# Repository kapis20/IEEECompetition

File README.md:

# IEEECompetition
This is the repo for IEEE Pitch Competition codes and files storage 

To run the code, you will need

1) Open CV (for windows: py -m pip install opencv-python)
2) numpy (for windows: py -m pip install numpy)
3) MediaPipe (for windows: pip install mediapipe) 

Note: Both squat and lateral raise code are essentially the same except for the angle calculation and display.

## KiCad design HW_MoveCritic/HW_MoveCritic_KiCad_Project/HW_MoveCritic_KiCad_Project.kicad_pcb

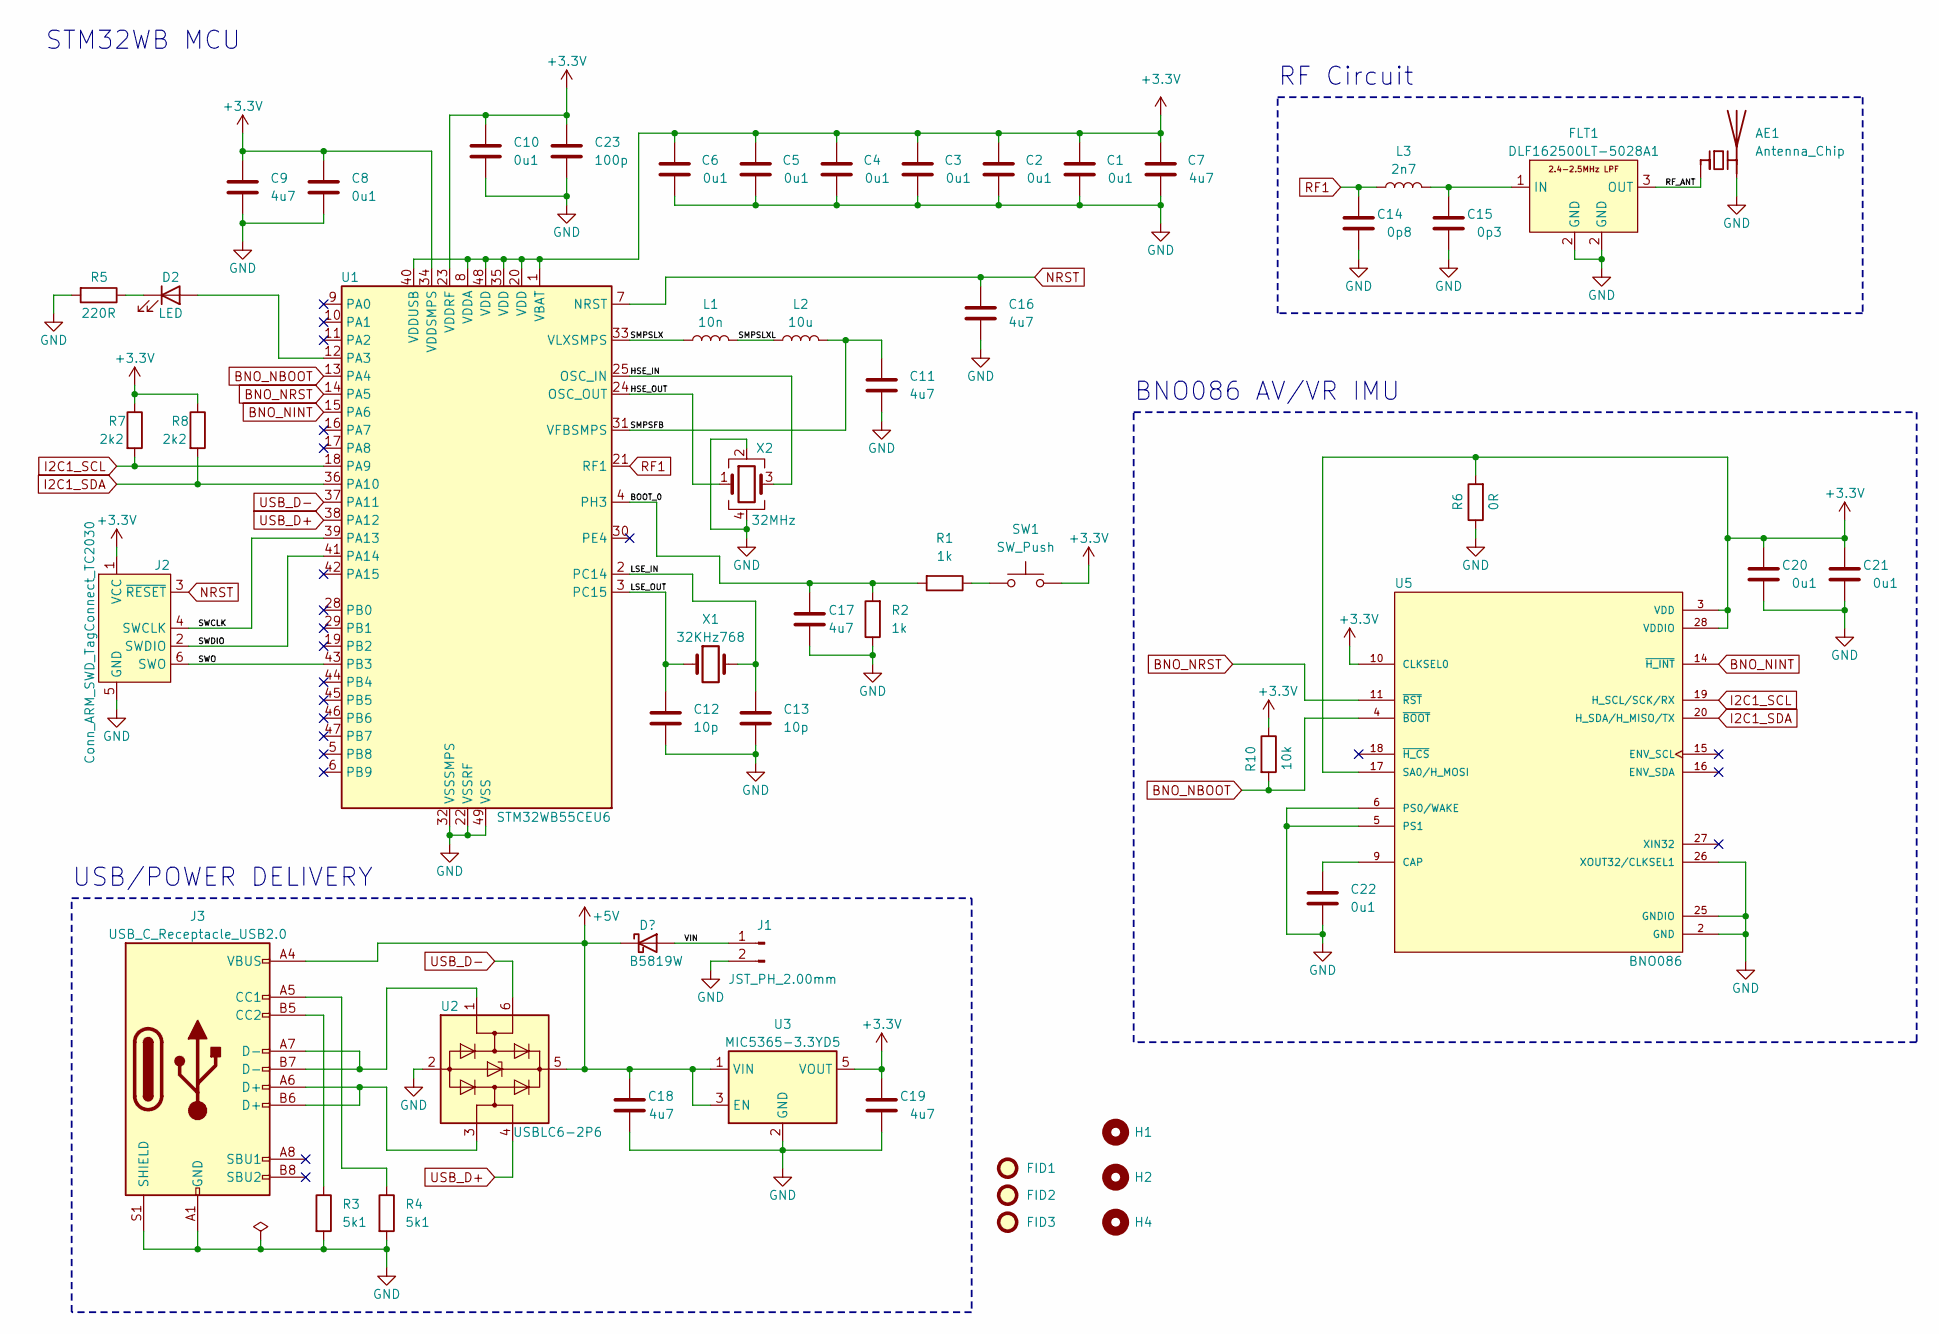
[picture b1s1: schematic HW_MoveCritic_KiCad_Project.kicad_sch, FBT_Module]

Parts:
AE1: Antenna_Chip; 2400MHz_PCB_Inverted_F
C1, C2, C3, C4, C5, C6, C8, C10, C20, C21, C22: 0u1; C_0201_0603Metric
C7, C9, C11, C16, C17, C18, C19: 4u7; C_0201_0603Metric
C12, C13: 10p; C_0402_1005Metric
C14: 0p8; C_0402_1005Metric
C15: 0p3; C_0402_1005Metric
C23: 100p; C_0201_0603Metric
D1: B5819W; D_SOD-123
D2: LED; LED_0402_1005Metric
FID1, FID2, FID3: Fiducial; Fiducial_1mm_Mask2mm
FLT1: DLF162500LT-5028A1
H1, H2, H4: MountingHole; MountingHole_2.2mm_M2_DIN965
J1: JST_PH_2.00mm; JST_PH_B2B-PH-K_1x02_P2.00mm_Vertical
J2: Conn_ARM_SWD_TagConnect_TC2030; Tag-Connect_TC2030-IDC-FP_2x03_P1.27mm_Vertical
J3: USB_C_Receptacle_USB2.0; USB_C_Receptacle_GCT_USB4105-xx-A_16P_TopMnt_Horizontal
L1: 10n; L_0402_1005Metric
L2: 10u; L_0805_2012Metric
L3: 2n7; L_0402_1005Metric
R1, R2: 1k; R_0603_1608Metric
R3, R4: 5k1; R_0402_1005Metric
R5: 220R; R_0201_0603Metric
R6: 0R; R_0603_1608Metric
R7, R8: 2k2; R_0402_1005Metric
R10: 10k; R_0402_1005Metric
SW1: SW_Push; PinHeader_1x02_P2.54mm_Vertical
U1: STM32WB55CEU6; QFN-48-1EP_7x7mm_P0.5mm_EP5.6x5.6mm
U2: USBLC6-2P6; SOT-666
U3: MIC5365-3.3YD5; SOT-23-5
U5: BNO086; LGA-28_5.2x3.8mm_P0.5mm; PARTREV 1.6
X1: 32KHz768; 830009678
X2: 32MHz; Crystal_SMD_TXC_7M-4Pin_3.2x2.5mm

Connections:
+3.3V: C1.1, C2.1, C3.1, C4.1, C5.1, C6.1, C7.1, C8.1, C9.1, C10.1, C19.1, C20.1, C21.1, C23.1, J2.1 (VCC), R6.2, R7.1, R8.1, R10.1, SW1.2, U1.1 (VBAT), U1.8 (VDDA), U1.20 (VDD), U1.23 (VDDRF), U1.34 (VDDSMPS), U1.35 (VDD), U1.40 (VDDUSB), U1.48 (VDD), U3.5 (VOUT), U5.3 (VDD), U5.10 (CLKSEL0), U5.17 (SA0/H_MOSI), U5.28 (VDDIO)
+5V: C18.1, D1.1 (K), J3.A4 (VBUS), J3.A9 (VBUS), J3.B4 (VBUS), J3.B9 (VBUS), U2.5 (VBUS), U3.1 (VIN), U3.3 (EN)
/BOOT_0: C17.1, R1.2, R2.2, U1.4 (PH3)
/HSE_IN: U1.25 (OSC_IN), X2.3
/HSE_OUT: U1.24 (OSC_OUT), X2.1
/LSE_IN: C13.1, U1.2 (PC14), X1.2
/LSE_OUT: C12.1, U1.3 (PC15), X1.1
/RF_ANT: AE1.1 (FEED), FLT1.3 (OUT)
/SMPSFB: C11.1, L2.2, U1.31 (VFBSMPS)
/SMPSLX: L1.1, U1.33 (VLXSMPS)
/SMPSLXL: L1.2, L2.1
/SWCLK: J2.4 (SWCLK), U1.39 (PA13)
/SWDIO: J2.2 (SWDIO), U1.41 (PA14)
/SWO: J2.6 (SWO), U1.43 (PB3)
/VIN: D1.2 (A), J1.1
BNO_NBOOT: R10.2, U1.13 (PA4), U5.4 (~BOOT)
BNO_NINT: U1.15 (PA6), U5.14 (~H_INT)
BNO_NRST: U1.14 (PA5), U5.11 (~RST)
GND: AE1.2 (PCB_Trace), C1.2, C2.2, C3.2, C4.2, C5.2, C6.2, C7.2, C8.2, C9.2, C10.2, C11.2, C12.2, C13.2, C14.2, C15.2, C16.2, C17.2, C18.2, C19.2, C20.2, C21.2, C22.2, C23.2, FLT1.2 (GND), J1.2, J2.5 (GND), J3.A1 (GND), J3.A12 (GND), J3.B1 (GND), J3.B12 (GND), J3.S1 (SHIELD), R2.1, R3.2, R4.2, R5.2, R6.1, U1.22 (VSSRF), U1.32 (VSSSMPS), U1.49 (VSS), U2.2 (GND), U3.2 (GND), U5.2 (GND), U5.5 (PS1), U5.6 (PS0/WAKE), U5.25 (GNDIO), U5.26 (XOUT32/CLKSEL1), X2.2, X2.4
I2C1_SCL: R7.2, U1.18 (PA9), U5.19 (H_SCL/SCK/RX)
I2C1_SDA: R8.2, U1.36 (PA10), U5.20 (H_SDA/H_MISO/TX)
NRST: C16.1, J2.3 (~RESET), U1.7 (NRST)
unnamed: D2.2 (A), U1.12 (PA3)
unnamed: D2.1 (K), R5.1
unnamed: C15.1, FLT1.1 (IN), L3.2
unnamed: J3.A5 (CC1), R4.1
unnamed: J3.B5 (CC2), R3.1
unnamed: J3.A6 (D+), J3.B6 (D+), U2.3 (I/O2)
unnamed: J3.A7 (D-), J3.B7 (D-), U2.1 (I/O1)
unnamed: R1.1, SW1.1
unnamed: C22.1, U5.9 (CAP)
RF1: C14.1, L3.1, U1.21 (RF1)
USB_D+: U1.38 (PA12), U2.4 (I/O2)
USB_D-: U1.37 (PA11), U2.6 (I/O1)

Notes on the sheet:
USB/POWER DELIVERY
STM32WB MCU
BNO086 AV/VR IMU
RF Circuit

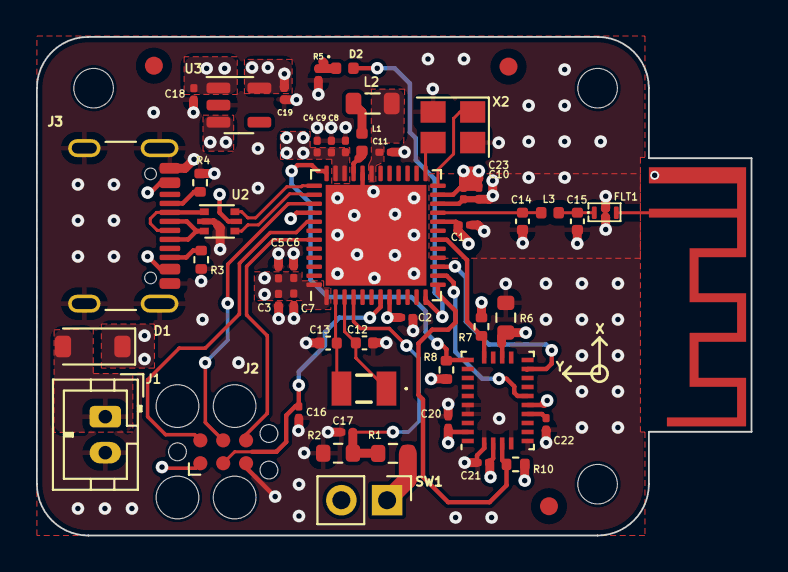
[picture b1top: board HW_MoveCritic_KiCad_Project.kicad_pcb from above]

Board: 4 copper layers, 39.7 x 27.7 mm, 55 parts (0 on the bottom side), 34 nets.

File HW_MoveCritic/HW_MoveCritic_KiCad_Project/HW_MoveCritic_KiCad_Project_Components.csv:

Source:,C:\Dev\IEEECompetition\HW_MoveCritic\HW_MoveCritic_KiCad_Project\HW_MoveCritic_KiCad_Project.kicad_sch,,,,,,,,
Date:,28/02/2024 13:18,,,,,,,,
Tool:,Eeschema 7.0.8,,,,,,,,
Generator:,C:\Program Files\KiCad\7.0\bin\scripting\plugins/bom_csv_grouped_by_value.py,,,,,,,,
Component Count:,45,,,,,,,,
,,,,,,,,,
Collated Components:,,,,,,,,,
,,,,,,,,,
Item,Qty,Reference(s),Value,LibPart,Footprint,Datasheet,Mfr_Part_Number,Price/unit (bulk 1000 units),Price/unit (prototype)
1,11,"C1, C2, C3, C4, C5, C6, C8, C10, C20, C21, C22",0u1,Device:C,Capacitor_SMD:C_0201_0603Metric,https://www.mouser.co.uk/datasheet/2/40/cx5r_KGM-3223198.pdf,KGM03AR51A104KN,0.063,0.344
2,7,"C7, C9, C11, C16, C17, C18, C19",4u7,Device:C,Capacitor_SMD:C_0201_0603Metric,https://www.mouser.co.uk/datasheet/2/40/cx5r_KGM-3223198.pdf,KGM03DR50J475MH,0.056,0.304
3,2,"C12, C13",10p,Device:C,Capacitor_SMD:C_0402_1005Metric,https://www.mouser.co.uk/datasheet/2/40/C0GNP0_KGM-3216332.pdf,KGM05ACG1C100KH,0.032,0.208
4,1,C14,0p8,Device:C,Capacitor_SMD:C_0402_1005Metric,https://www.mouser.co.uk/datasheet/2/447/KEM_C1121_CBR_AUTO-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,CBR04C808B5GACAUTO,0.015,0.128
5,1,C15,0p3,Device:C,Capacitor_SMD:C_0402_1005Metric,https://www.mouser.co.uk/datasheet/2/281/1/GRM1555C1HR30BA01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,GRM1555C1HR30BA01J,0.009,0.08
6,1,C23,100p,Device:C,Capacitor_SMD:C_0201_0603Metric,https://www.mouser.co.uk/datasheet/2/40/KGM_X7R-3223212.pdf,KGM03AR71H101KH,0.03,0.08
7,1,D1,B5819W,Device:D_Schottky,Diode_SMD:D_SOD-123,https://www.mouser.co.uk/datasheet/2/258/B5817W_B5819W_SOD_1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,B5819W-TP,0.031,0.216
8,1,D2,Red,Device:D_LED,Diode_SMD:C_0402_1005Metric,https://www.we-online.com/components/products/datasheet/1500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,150040RS73240,0.132,0.256
9,1,FLT1,DLF162500LT-5028A1,MoveCritic_HW_Schematic_Symbols:DLF162500LT-5028A1,HW_MoveCritic_Footprints:DLF162500LT-5028A1,https://product.tdk.com/system/files/dam/doc/product/rf/rf/f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,DLF162500LT-5028A1,0.173,0.4
10,1,J3,USB_C_Receptacle_USB2.0,Connector:USB_C_Receptacle_USB2.0,Connector_USB:USB_C_Receptacle_GCT_USB4105-xx-A_16P_TopMnt_Horizontal,https://www.mouser.co.uk/datasheet/2/837/Global_Connector_Te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,USB4105-GF-A-120,0.292,0.664
11,1,L1,10n,Device:L,Inductor_SMD:L_0402_1005Metric,https://productfinder.pulseelectronics.com/api/open/part-att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,ASCH0010050510NJCP,0.02234,0.08
12,1,L2,10u,Device:L,Inductor_SMD:L_0805_2012Metric,https://www.mouser.co.uk/datasheet/2/396/Taiyo_Yuden_LSQ02_e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,LSQNA201212T100KR,0.052,0.16
13,1,L3,2n7,Device:L,Inductor_SMD:L_0402_1005Metric,https://www.mouser.co.uk/datasheet/2/281/1/JELF243B_0010-169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,LQG15HS2N7S02,0.01624,0.08
14,2,"R1, R2",1k,Device:R,Resistor_SMD:R_0603_1608Metric,https://www.mouser.co.uk/datasheet/2/315/AOA0000C307-1149632.pdf,ERA-3ARW102V,0.191,0.792
15,2,"R3, R4",5k1,Device:R,Resistor_SMD:R_0402_1005Metric,https://www.mouser.co.uk/datasheet/2/447/PYu_RP_51_RoHS_L_0-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,RP0402BRD075K1L,0.048,0.328
16,1,R6,0R,Device:R,Resistor_SMD:R_0603_1608Metric,https://www.vishay.com/docs/28744/mc_vg01.pdf,MCT0603HZ0000ZP500,0.09,0.48
17,2,"R7, R8",2k2,Device:R,Resistor_SMD:R_0402_1005Metric,https://www.mouser.co.uk/datasheet/2/315/Panasonic_ERA-3305500.pdf,ERA-2VEB2201X,0.087,0.288
18,1,R10,10k,Device:R,Resistor_SMD:R_0402_1005Metric,https://www.vishay.com/docs/20035/dcrcwe3.pdf,CRCW040210K0FKEDC,0.003,0.08
19,1,R5,220R,Device:R,Resistor_SMD:C_0201_0603Metric,https://www.mouser.co.uk/datasheet/2/315/AOA0000C304-1149620.pdf,ERJ-1GJF2200C,0.02,0.152
20,1,U1,STM32WB55CEU6,MCU_ST_STM32WB:STM32WB55CEUx,Package_DFN_QFN:QFN-48-1EP_7x7mm_P0.5mm_EP5.6x5.6mm,https://www.mouser.co.uk/datasheet/2/389/dm00344191-1798909.pdf,STM32WB55CEU6,2.84,3.8
21,1,U2,USBLC6-2P6,Power_Protection:USBLC6-2P6,Package_TO_SOT_SMD:SOT-666,https://www.mouser.co.uk/datasheet/2/389/cd00050750-1796222.pdf,USBLC6-2P6,0.163,0.472
22,1,U3,MIC5365-3.3YD5,Regulator_Linear:MIC5365-3.3YD5,Package_TO_SOT_SMD:SOT-23-5,https://www.mouser.co.uk/datasheet/2/268/mic5365-1082359.pdf,MIC5365-3.3YD5-TR,0.128,0.176
23,1,U5,BNO086,BNO080:BNO080,Package_LGA:LGA-28_5.2x3.8mm_P0.5mm,https://www.mouser.co.uk/datasheet/2/1480/BNO080_085_Datashe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,BNO086,7.53,13.29
24,1,X1,32KHz768,Device:Crystal,830009678,https://www.we-online.com/components/products/datasheet/8300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,830009678,0.271,0.512
25,1,X2,32MHz,Device:Crystal_GND24,Crystal:Crystal_SMD_TXC_7M-4Pin_3.2x2.5mm,https://www.mouser.co.uk/datasheet/2/741/LFXTAL061677Reel-15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,LFXTAL061677Reel,0.344,0.6
,,,,,,,,13.96258,30.85
,,,,,,,PCBway manufacture,,
,,,,,,,PCBway Fabrication,,
,,,,,,,Shipping,,

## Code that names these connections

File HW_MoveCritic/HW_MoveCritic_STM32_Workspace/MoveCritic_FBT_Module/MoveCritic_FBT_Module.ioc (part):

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Mcu.Name=STM32WB55CEUx
Mcu.Package=UFQFPN48
Mcu.UserName=STM32WB55CEUx
PA10.Signal=I2C1_SDA
PA11.Mode=Device
PA11.Signal=USB_DM
PA12.Mode=Device
PA12.Signal=USB_DP
PA13.Mode=Trace_Asynchronous_SW
PA13.Signal=SYS_JTMS-SWDIO
PA14.Mode=Trace_Asynchronous_SW
PA14.Signal=SYS_JTCK-SWCLK
PA3.GPIOParameters=GPIO_Label
PA3.GPIO_Label=TIM2_CH4_LED
PA3.Signal=S_TIM2_CH4
PA4.GPIOParameters=GPIO_Label
PA4.GPIO_Label=SPI1_CS
PA4.Signal=GPIO_Output
PA5.Mode=Full_Duplex_Master
PA5.Signal=SPI1_SCK
PA6.Mode=Full_Duplex_Master
PA6.Signal=SPI1_MISO
PA7.Mode=Full_Duplex_Master
PA7.Signal=SPI1_MOSI
PA8.GPIOParameters=GPIO_Label
PA8.GPIO_Label=IMU_INT
PA8.Signal=GPIO_Output
PA9.Signal=I2C1_SCL
PB3.Mode=Trace_Asynchronous_SW
PB3.Signal=SYS_JTDO-SWO
PC14-OSC32_IN.Mode=LSE-External-Oscillator
PC14-OSC32_IN.Signal=RCC_OSC32_IN
PC15-OSC32_OUT.Mode=LSE-External-Oscillator
PC15-OSC32_OUT.Signal=RCC_OSC32_OUT
RCC.HSE_VALUE=32000000
RCC.SYSCLKFreq_VALUE=64000000
RCC.SYSCLKSource=RCC_SYSCLKSOURCE_PLLCLK
board=custom

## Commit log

2023-12-22 Add files via upload
    V1 of code for squat and lateral raise exercises
2024-01-11 Successfully generated a new code that works for squats when the camera is positioned in front of the person. In addition, we can use the smartphone camera wirelessly. Also added a scale factor that 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
2024-02-06 Adds class to intercept UDP packets from SlimeVR server
2024-02-07 Adds ESP tracker firmware
2024-02-08 Performance optimisation using blocking UDP server instead of threading server
2024-02-13 angles updated
2024-02-16 Adds KICAD and STM32CubeMX env for the development of a custom tracking module
2024-02-23 V0.1 - Complete Schematic, layout incomplete
2024-04-08 SlimeVR Final Commit
2024-04-08 Large Commit for HW design
2024-04-08 Adds methods for mediapipe post-processing of mp4
2024-04-21 Files to store data on fly added - need to still sort out python issue to combine and test it with the mediapipe code
